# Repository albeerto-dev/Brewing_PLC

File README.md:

# Fellow Brewer - PLC 
Un sistema automatico per la produzione del mosto di birra:
PLC programmato tramite piattaforma CODESYS in IEC61131 e l'utilizzo di una Raspberry Pi per la gestione di I/O con l'utilizzo di una HMI accessibile tramite WebServer.
Sviluppato da Alberto M. Ramagini

## Obiettivi di sviluppo 
*Codice*
- [x] Struttura generale delle varibili globali e SFC / LD / ST
- [x] Implementazione modalità manuale
- [x] Implementazione modalità automatica
- [x] Implementazione allarmi
- [x] Implementazione I/O
- [x] Implementzaione timer 
- [x] Implementazione PID
- [x] Implementazione ON/OFF
- [x] Implementazione voce MAIN
- [x] Implementazione voce BREW
- [x] Implementazione voce RECIPE

*Wiring*
- [x] Bozza su breadboard
- [x] Disegno PCB
- [x] Realizzazione PCB
- [x] Assemblaggio PCB
- [x] Cablaggio bassa tensione
- [x] Disegno schema circuito bassa tensione
- [x] Cablaggio alta tensione 
- [x] Disegno schema circuito alta tensione

*Test di funzionamento*
- [x] Input e output basilare
- [x] Batch con sola acqua
- [x] Batch di produzione mosto di birra

## Aggiornamenti di sviluppo
* Resoconto 19.06.2020 //
Dall'imagine 1 si denota la prima struttura dell'interfaccia HMI che consentirà di gestire la varia attrezzera tramite pannello "Settings..." di visualizare "DATA" di poter usare il controllore in modlaità manule "MAIN" e di poter procedere con una completa cotta con la modalità "START A BREW" che consete di insererire una ricetta tramite file .xml o crearla sul momento.
* Resoconto 22.06.2020 // 
Prime prove di struttura codice PID. Procede con complicazioni la gestione dell'impulso basato sui calcoli dell'algoritmo PID. Questa prima versione è basata sul codice in C++ di un precedente progetto personale. La difficolta sta nel tramutare il valore di errore di tipo REAL in un impulso dell'attuatore di una durata consona ed efficace da applicare secondo una finestra temporale di azione da parte dell'SSR.
* Resoconto 25.06.2020 //

Codice PID ultimato. Tramite prove di simulazione sono riuscito a gestire il valore di output PID.Y in maniera tale da produrre un impulso di una certa lunghezza temporale per l'attivazione dell'SSR. Manca il tuning dei parametri.
* Resoconto 28.06.2020 //           
     
Interfaccia MAIN ultimata. Tutti i pulsanti sono stati introdotti. Gli SSR di HLT e BOIL seguono un algoritmo di tipo ON/OFF per il riscaldamento e la tenuta a SET POINT. L'SSR del MASH TUN invece ha la doppia possibilità di eseguire il controllo tramite algoritmo ON/OFF oppure di tipo PID (oppurtunamente tarato) semplicemente premendo il pulsante apposito. I due algoritmi di controllo temperatura sono stati introdotti nel programma tramite FUNCTION BLOCK per avere una maggiore versatilità nel codice. La funzionalità del timer ha come unico scopo la funzione di disattivare l'SSR a fine countdown. Ho implementato un pulsante di EMERGENZA per disattivare tutti gli attuatori contemporaneamente. La struttura del codice è per ora interamente in TESTO STRUTTURATO (ST).
* Resoconto 05.08.2020 //
Ripreso lo sviluppo del codice da circa una settimana dopo la puasa esami e estiva. Dopo svariati tentativi di utilizzo della libreria RecipeMangaer per la gestione delle ricette avevo inizialmente deciso di abbandonarne l'utilizzo. La pessima documentazione la rendeva inutilizzabile, ma da pochissimi giorni CODESYS Italia ha pubblicato su Youtube un video esplicativo dell'utilizzo della libreria. Al momento sembra essere il tutorial più completo ed efficace dato che le uniche risorse online sono un paio di domande sui forum dedicati e altri due video su Youtube, di cui uno in russo (incomprensibile) e uno in inglese totalmente inutile e inefficace all'apprendimento. Ripongo estrema fiducia nel risucire ad implementare la gestione delle ricette (salvataggio/caricamento/scrittura/utilizzo) in un arco di tempo relativamente breve. Ad oggi la parte complessa di implementazione risulta essere lo storage, il caricamento e la lettura dei file in .txtrecipe .  
* Resoconto 15.10.2020 //

Finalmente sono arrivato ad un punto di svolta. Da come si vede nell'immagine, sono riuscito a implementare la scrittura e lo storage delle ricette. La lista di sinistra indica i nomi delle ricette create e disponibili, il riquadro centrale fa visualizzare i file interni alla cartella dove vengono salvate le ricette con i relativi nomi. Sotto alla finestra di navigazione è presente l'interfaccia di scrittura delle varibaili da registrare nella ricetta/file da salvare o creare. Sulla destra si trovano una moltitudine di funzionalità a pulsante che corrispondono ad alcuni dei metodi che vengono forniti dalla libreria RecipeManager che ho deciso di implementare. Probabilmente alcune di queste funzionalità non sono strettamente utili e in futuro qualcuna sarà probabilmente eliminata. Il prossimo passo consiste nell'implementare la modalità automatica che funziona se e solo se si seleziona un file RICETTA precedentemento creato; dopo aver selezionato il file, il programma salva le varibili in una struct temporanea in cui si trovano i parametri che seguirà il processo durante la birrificazione
* Resoconto 16.10.2020 //

Risolto il problema di lettura al momento della selezione della ricetta. Ho appena iniziato lo sviluppo della modalità automatica e si possono già ben vedere tutti i pre-requisiti da soddisfare prima di comiciare la cotta : caricamento dell'acqua e selezione della ricetta (che se mal selezionata genera errore; la selezione avviene tramite scrittura del nome della ricetta nell'apposito riquadro). Ho pensato anche di inserire una progressbar per indicare lo status temporale della cotta e ho avuto l'idea di implementare una modalità semi-automatica che può essere attivata e disattivata a piacimento durante la cotta.
* Resoconto 19.10.2020 // 
Oggi è una buona giornata di commit. Sono stati raggiunti ottimi risultati. Dopo aver recentemente introdotto la lettura delle ricette, ho ora completato l'implementazione della parte interamente automatica. Il meccanismo di utilizzo è come segue: come prima cosa si spuntano le checkbox di verifica di inserimento acqua nelle pentole di impianto. Dopo ciò è possibile selezionare la ricetta, precedentemente creata tramite l'apposito menu "RECIPE". Avvenuto il salvataggio nelle variabili globali, comincia il riscaldamento dell'acqua in entrambe le pentole (se si fa sparge, altrimenti viene riscaldata solo quella di mash). Un avviso indicherà l'inserimento dei grani per iniziare l'ammostamento e dopo averli inseriti si confermerà tramite slider che darà il via a tutti gli step del mash con relativo tempo e temperatura. Terminato il mash si può procedere con lo sparge a corretta temperatura grazie all'azione paralella durante l'azione di ammostamento. Una volta confermato l'inizio di sparge tramite slider, il timer parte. Terminato il timer si richiede all'operatore di confemrare il trasferimento del mosto nel tino di bollitura tramite slider. Una volta confermato si attiva l'SSR del tino di bollitura per portare il  mosto ad ebollizione. Raggiunti circa i 96°C si chiede conferma all'operatore per l'inizio della bollitura tramite slider. Una volta confermato, si attiva il timer di controllo durata della bollitura e in contemporanea una spia luminosa (e sonora in futuro) che avvisa l'operatore di confermare la gettata di luppolo. Terminata la bollitura si disattiva l'SSR della termoresistenza riscaldante e si attiva il relay dell'elettovalvola di raffreddamento o per arrivare a temperatura di hopstand (se richiesto da ricetta) oppure per raffredare il mosto a temperatura di inoculo del lievito. La giornata di cotta è terminata. 
Nell'immagine di destra si possono osservare tutte le POU e le FB del codice, alcune sono ridondanti, altre no, altre saranno eliminate pechè non utili, ma in linea di massima dovrebbero essere quelle definitive. Inserisco anche un'immagine della HMI dedicata alla modalità automatica abbastanza semplice ed essenziale e che non crei confusione all'operatore. All'interno della cartella images ho allegato anche il DEBUG visivo di una simulazione di cotta tramite valori forzatamente scritti all'interno del PLC per verificare il corretto funzionamento.
* Resoconto 24.10.2020 //
Il progetto cambia ufficialmente nome e diventa "FELLOW BREWER" che dall'inglese può essere tradotto con "collega birraio". Ho scelto questo nome perchè risalta l'importanza di un "collega" durante un faticoso e complesso processo produttivo come quello della produzione del mosto di birra. Collega perchè aiuta a portare a termine i compiti di produzione nel modo più efficiente possibile, riducendo i rischi e aumentado la replicabilità del processo. FELLOW BREWER è un collega/assistente a tutti gli effetti.
Questo resoconto è l'ultimo riguardante lo sviluppo del codice: lo sviluppo software è terminato (salvo eventi eccezionali per aggiungere funzionalità non ancora pensate).
Tutti i bug sono stati risolti e tutti tutte le funzionalità sono state implementate correttamente. Il cuore del sistema è chiaramente la funzionalità BREW che consente di produrre un batch in modalità automatica con qualche accortezza da parte dell'operatore. Quest'ultimo dovrà rispondere al PLC durante la cotta così da verificare se alcuni passaggi siano stati effettuati e se si possa procedere allo step successivo. Seguiranno poi spiegazioni più dettagliate alla stesura della tesi o anche in un video spiegazione del codice scritto (ampiamente commentato). Questa è l'HMI:
    
* Resonto 27.10.2020 //
Gli schemi elettrici sono stati disegnati tramite KiCAD e completati al meglio. Potrebbero esserci delle modifiche in futuro ma comunque il grosso è stato realizzato. Ho disegnato 2 schemi elttrici: uno approfondisce i collegamenti 5VDC dei PIN della Raspberry Pi con qualche aggiunta di componenti in 220VAC e 12VDC per chiarezza e completezza di progetto; l'altro invece approfondisce il circuito in 220VAC e a 12VDC sfruttati dai segnali della Rappberry Pi. Manca un terzo circuito dove i collegamenti agli attuatori e sensori sono "eliminati" per fare posto alle morsettiere di collegamento che saranno utili sia nella progettazzione della "HAT" (il PCB) sia nel cablaggio del protipo finale.
* Resoconto 02.11.2020 //
Tutti i circuti sono stati disegnati. Ho mandato in stampa il PCB tramite il portale pcbway.com e tra qualche giorno dovrebbe essere consegnato. Ho avuto la necessità di realizzare: il disegno circuito in 220VAC con l'aggiunta del convertitore 12VDC, il disegno del circuito degli I/O della Raspberry Pi con gli elementi controllati, il disegno del circuito degli I/O della Raspberry Pi con la morsettiere dei vari componenti di progetto (utili alla realizzazione del PCB).All'interno della cartella di reposistory "Schemi e PCB" si possono trovare i file PDF di cui ho scritto. Qui sotto i disegni realizzati:     
* Resoconto 09.11.2020 // Il pacco da pcbway.com contente il PCB è stato consegnato. Potrò procedere con l'assemblaggio e la saldatura dei componenti soltanto intorno alla terza o quarta settimana di dicembre dopo aver terminato il corso di formazione in "Tecnologie Birrarie" presso il CERB dell' Università degli Studi di Perugia. 
* Resoconto 22.12.2020 // Ho saldato e testato tutti i componenti saldati sulla scheda sia tramite test pilotati dal PLC sia tramite tester per verificare il corretto voltaggio degli output. Tutti i led e tutti gli attuatori funzionanano regolarmente. Il funzionamento delle sonde di temperatura DS18B20D è stato verificato tramite l'interfaccia grafica che ha correttamente segnalato la temperatura rilevata.

* Resoconto 15.01.2021 // Il progetto è completato.                              
  
* Resoconto 26.01.2021//
Video dimostrativo del funzionamento del PLC, di tutti i suoi input e output e comprensivo anche di una spiegazione di massima di alcune scelte progettuali sia software che hardaware.

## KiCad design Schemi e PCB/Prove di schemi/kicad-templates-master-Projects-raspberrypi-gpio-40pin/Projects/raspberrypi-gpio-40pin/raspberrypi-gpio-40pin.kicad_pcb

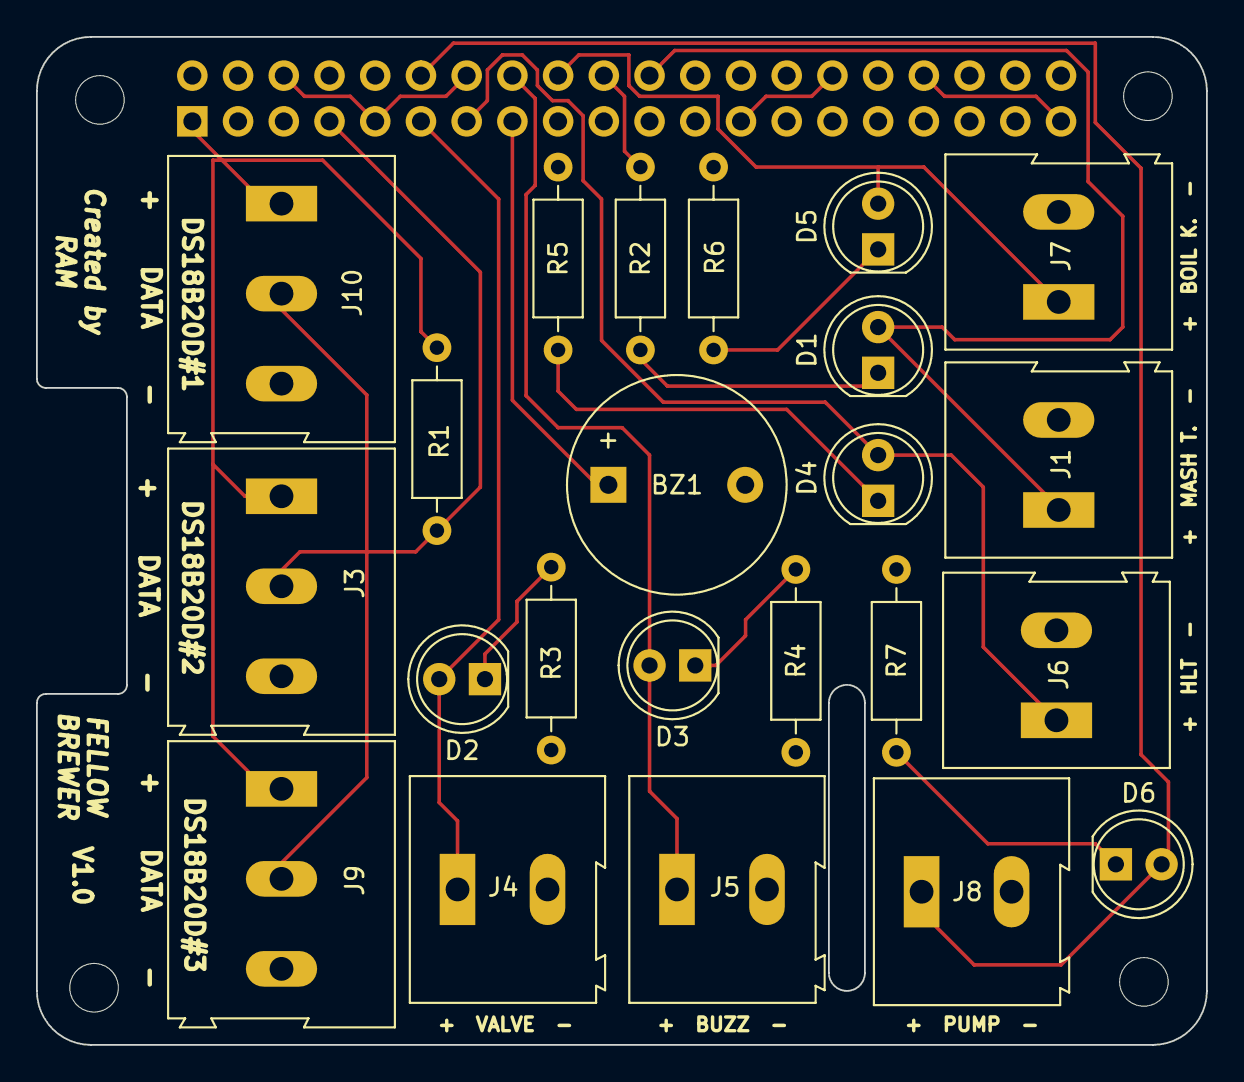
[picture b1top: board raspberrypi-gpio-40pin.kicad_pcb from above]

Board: 2 copper layers, 65.0 x 56.0 mm, 28 parts (1 on the bottom side), 16 nets.

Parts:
BZ1: Buzzer; Buzzer_12x9.5RM7.6
D1, D2, D3, D4, D5, D6: LED; LED_D5.0mm
J1: Terminal SSR mash; TerminalBlock_Altech_AK300-2_P5.00mm
J2: Raspberry Pi 4; PinSocket_2x20_P2.54mm_Vertical
J3: Morsettiera DS18B20 #1; TerminalBlock_Altech_AK300-3_P5.00mm
J4: Terminal Relay chill valve; TerminalBlock_Altech_AK300-2_P5.00mm
J5: Terminal Buzzer Alarm; TerminalBlock_Altech_AK300-2_P5.00mm
J6: Terminal SSR sparge; TerminalBlock_Altech_AK300-2_P5.00mm
J7: Terminal SSR boil; TerminalBlock_Altech_AK300-2_P5.00mm
J8: Terminal SSR pump; TerminalBlock_Altech_AK300-2_P5.00mm
J9: Morsettiera DS18B20 #2; TerminalBlock_Altech_AK300-3_P5.00mm
J10: Morsettiera DS18B20 #3; TerminalBlock_Altech_AK300-3_P5.00mm
MK1, MK2, MK3, MK4: M2.5; MountingHole_2.7mm_M2.5
R1: 4k7; R_Axial_DIN0207_L6.3mm_D2.5mm_P10.16mm_Horizontal
R2, R3, R4, R5, R6, R7: 100; R_Axial_DIN0207_L6.3mm_D2.5mm_P10.16mm_Horizontal

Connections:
+3V3: J2.1, J3.1, J9.1, J10.1, R1.1
GND: BZ1.2, J1.2, J2.6, J2.9, J2.14, J2.20, J2.25, J2.30, J2.34, J2.39, J3.3, J4.2, J5.2, J6.2, J7.2, J8.2, J9.3, J10.3, R2.1, R3.1, R4.1, R5.1, R6.1, R7.1
unnamed: BZ1.1, J2.15
unnamed: D1.1, R2.2
unnamed: D1.2, J1.1, J2.22
unnamed: D2.1, R3.2
unnamed: D2.2, J2.11, J4.1
unnamed: D3.1, R4.2
unnamed: D3.2, J2.16, J5.1
unnamed: D4.1, R5.2
unnamed: D4.2, J2.13, J6.1
unnamed: D5.1, R6.2
unnamed: D5.2, J2.18, J7.1
unnamed: D6.1, R7.2
unnamed: D6.2, J2.12, J8.1
unnamed: J2.7, J3.2, J9.2, J10.2, R1.2

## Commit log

2020-06-18 LED e DS18B20
    Prime prove di funzionamento del web server con accensione e spegnimeto LED tramite HMI e rilevazione temperatura con sensore DS18B20 con protocollo di comunicazione OneWire
2020-06-18 Update LED_e_TEMP_DS18B20.project.~u
2020-06-19 Display valori sensore e crazione schede
    Stampa a schermo dei valori del sensore di temperatura e prime bozze di struttura HMI con creazione di diverse schede in supporto alla principale
2020-06-19 Progressi HMI
    Sviluppo HMI di base
2020-06-19 Progressi nello sviluppo HMI e prima impostazione di utilizzo del stistema PLC
    Dall'imagine 1 si denota la prima struttura dell'interfaccia HMI che consentirà di gestire la varia attrezzera tramite pannello "Settings..." di visualizare "DATA" di poter usare il controllore in mo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
2020-06-19 Caricamento IMMAGINE_01
    Immagine 01
2020-06-20 Progressi in HMI e strutturazione
    HMI migliorata e inizio di programmazione del PID
2020-06-22 Prima prove di struttura codice PID
    Prime prove non funzionanti data la difficoltà nel tramutare un tipo REAL in una varibile di tempo corrispondente alla finestra temporale dell'impulso.
2020-06-25 PID funzionante
    Algoritmo PID adattato al'uscita per il funzionaento su un SSR
2020-06-25 Image
2020-06-25 HMI upgrade
    Prima bozza dell'impostazione del timer
2020-06-28 Interfaccia e funzionamento MAIN semicompletata
    Tutti gli SSR e pulsanti abilitati. Manca l'implementeazione degli allarmi e il tuning del PID
2020-06-28 Creazione cartella Images per README
2020-10-02 Prime impostazioni del riquadro ricette
    Il pannello RICETTE comincia a prendere forma, la sta reputando la parte più complessa della scrittura del codice. Molto complesso da gestire.
2020-10-05 Implementazione libreria RecipeManager
    Primi passi nell'implementazione della libreria
2020-10-06 Creazione FB per crazione ricette
    Un FB dotato di 3 metodi : Directoring, Loading e Saving è stato introdotto nel codice, ancora non risulta essere pienamente funzionante ma ripongo grande fiducia nello sviluppo dei prossimi giorni
2020-10-15 Scrittura e storage ricetta
    Implementazione di scrittura salvataggio e storage di una ricetta
2020-10-16 Sviluppo modalità automatica
    Primi passi nello sviluppo della modalità automatica
2020-10-19 Modalità automatica implementata
    Mancano solo poche rifiniture per un corretto funzionamento. HMI e automazione implementata
2020-10-24 Final
    Realizzazzione del codice nella stua stuttura totale è terminata
2020-10-24 Upload HMI
2020-10-27 Upload schemi elettrici
2020-11-02 Upload schemi elettrici e piccole modifiche al codice
    Ho introdotto nel codice la lettura delle 3 sonde DS18B20D
2020-11-09 Upload PCB consegnato
2020-12-22 Upload PCB ass
2021-01-16 Rimappatura GPIO
2021-01-26 Progetto completato
